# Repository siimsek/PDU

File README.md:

# Açık çevrim buck güç katı

20–26 V girişten (6S batarya, ana çalışma noktası 24,6 V) 11 V / 7,5 A (82,5 W) hedefleyen tek faz, asenkron, açık çevrim buck güç katı. Modül 0–7,5 A zarfında farklı uyumlu yükler içindir; T3 Gemstone O1 ve SLAMTEC RPLIDAR S2E referans yüklerdir.

**Aşama: ANA GÜÇ DEVRESİ.** Güç katının değerleri belirlendi ve LTspice'ta sınandı; parçalar için aday listesi var, kesin seçim yapılmadı. PWM, geri besleme ve soft-start henüz yok; fiziksel devre kurulmadı.

**Güncel yol:** Önce gereksinimler ve kontrol/sürücü/koruma mimarisi belirlenir; sonra kontrolcü ile güç katı adayları birlikte değerlendirilir ve parçalar kullanıcıyla kesinleştirilir. Bobin için 33 µH başlangıç hedefidir; kapalı çevrim uyumu ve gerçek sarım ölçümü henüz yoktur. Devamında gerçek değerlerle simülasyon ve tezgâh doğrulaması yapılır. [Yol haritası](YOL-HARITASI.md) bağımlılıkları ve açık işleri gösterir.

**Dondurma durumu: FROZEN (12 Kasım 2026, simülasyon dondurması).** Çıkışa paralel `Cd = 470 µF + seri Rd = 0,22 Ω` sönüm dalı eklendi. Örneklenen model setlerinde 200 ms ve ayrı bir köşede 500 ms sabit güç darbeleri sönümlü raporlandı; bütün yük, sıcaklık ve tolerans kombinasyonları doğrulanmış değildir. Gerilim sınıfları **Cout ve Cd ≥ 35 V**, **Cin ≥ 50 V** olarak belirlendi. Açık çevrim güvenli 11 V regülasyonu sağlamaz; fiziksel ölçüm yoktur ve hassas yükler bağlanmamalıdır. Kanıt ve kalan işler: [buck/OPTIMIZASYON.md](buck/OPTIMIZASYON.md) §12–13.

**Kontrol yöntemi araştırması:** Depodaki açık çevrim testleri ile dışarıdaki kapalı çevrim model denemeleri ayrı tutuldu. İlk LT3844, Type-III ve ortalama-akım sonuçlarının tarihçesi [OPTIMIZASYON.md](buck/OPTIMIZASYON.md) §14–15'tedir; son tekrar, ön puan ve güç katı değişikliği hesabı §16'dadır.

**Kapalı çevrim son tekrar (14 Kasım 2026):** LT3844 F sabit-frekans tepe-akım makromodeli 20 µs yük rampasında 10,794–11,165 V, 20–26–20 V / 200 ms sabit-güç koşusunda 10,904–11,043 V verdi; bobin akımından yaklaşık 99,95 kHz doğrulandı. Modeldeki 9,76 mΩ seri akım algısı direnci dondurulmuş güç yolunda yok ve 7,5 A'ta 0,549 W HESAP kaybı ekler. Type-III Ki=200 / 9 A **ideal** akım kesimi 20 µs rampasında 9,809–11,478 V verdi; yüksüz 20 V için tamamlanmış 120 ms simülasyonda 48 ms referans rampasıyla çıkış 11,413 V tepe / 11,410 V geç değer oldu. Histeretik 25 mV modelinin çıkış aralığı daha dardı, ancak frekansı girişe göre 93,7–121,2 kHz değiştirdi. 100 kHz için LT3844 tipi kontrol en güçlü dinamik referans; güç yolu aynen korunacaksa gerçek akım algısı henüz kanıtlanmadı. Aynı puanlama altında 90 üzeri ön puan kuramsal olarak mümkün, ancak güç katı uyumunu ve kaybı iyileştirmek tek başına yaklaşık 86 puanla sınırlı kalır; diğer puan başlıklarında da ek kanıt gerekir. DCR akım algısı düşük etkili araştırma adayıdır, henüz test edilmedi ve asenkron kata doğrudan uyumu gösterilmedi. Ön puan, hesap ve riskler [buck/OPTIMIZASYON.md](buck/OPTIMIZASYON.md) §16.4–16.7'dedir. Mimari/parça seçilmedi; bağımsız OVP doğrulanmadığından gerçek O1/S2E bağlanmaz.

**Nerede kaldık, sırada ne var:** [YOL-HARITASI.md](YOL-HARITASI.md) · **Çalışma kuralları (yapay zekâ araçları dahil):** [AGENTS.md](AGENTS.md)

## Devre değerleri ve parçalar

| Eleman | Şematikteki değer | 1. sıra aday (kesin değil) | Kabul aralığı |
|---|---|---|---|
| V1 | 24,6 V | 6S batarya | 20–26 V |
| Vdrv | 100 kHz, Ton = 4,59 µs | — (sonraki aşamada sürücü + PWM) | — |
| L1 | 33 µH el sarım, DCR 7,81 mΩ (HESAP, 20 °C) | Magnetics Kool Mµ 40µ `0077536A7`, 22 sarım, 100 × 0,20 mm litz (2. sıra: satın alma, Würth 74435583300) | **33 µH** (el sarım 30,7–36,1 µH öngörü; satın alma ±%20 için örnek köşeler sınandı); DCR 6,5–15 mΩ (el sarım hedefi 7,5–10 mΩ); 12 A'de L ≈ %95 (HESAP) |
| Cout | 1000 µF, ESR 35 mΩ (**maks. empedans, ESR varsayımı**) | Nichicon UHE1E102MHD6TO *(elektriksel R/C referansı; kesin parça ≥35 V seçilecek)* | 1000 µF ±%20, ESR ≤ 35 mΩ, **≥ 35 V** (S1 kısa devresinde 27,3–31,1 V) |
| Cd + Rd | 470 µF + seri 0,22 Ω (çıkış sönüm dalı) | — (dondurma sonrası seçilecek) | Cd: 470 µF ±%20, **≥ 35 V**; Rd: 0,22 Ω (Rd + Cd_ESR toplamı **0,15–0,60 Ω**), ≥ 0,25 W |
| Cin1, Cin2 | 2 × 1000 µF, ESR 15 mΩ | 2 × TDK B41859D7108M000 *(elektriksel R/C referansı; kesin parça ≥50 V seçilecek)* | toplam ripple akımı ≥ 4,5 A, **≥ 50 V**; örnek sıcak takma hesabı 48,0 V, gerçek kaynak ve pay doğrulanmadı |
| S1 | ideal anahtar, `Ron=5.6m` | STP100N6F7 (60 V, TO-220) | RDS(on) ≤ 12 mΩ, VDS ≥ 55 V |
| D1 | ideal diyot, `Vf=0.38 Ron=8m` | STPS40M60CT (60 V, 2 × 20 A, iki bacak paralel) | VF ≤ 0,58 V @ 7,5 A, VRRM ≥ 45 V |
| Rload | 1,467 Ω | ≥ 100 W direnç yükü | — |

Şematik ideal elemanlıdır; değerler aday listesinin başındaki parçaların veri sayfasından alınmıştır. Bu bir satın alma kararı değildir. Adayların sırası ve nedeni, doğrulama durumu ve kriterlerin nedenleri: [buck/PARCA-HEDEFLERI.md](buck/PARCA-HEDEFLERI.md). Seçim süreci ve test sonuçları: [buck/OPTIMIZASYON.md](buck/OPTIMIZASYON.md).

LTspice sonucu (24,6 V giriş, kararlı durum, 19–20 ms): Vo = 11,000 V, çıkış ripple'ı 55,7 mV t-t, bobin akımı 6,56–8,44 A. Fiziksel ölçüm yoktur.

Açık çevrim: Ton sabitken giriş veya yük değişirse çıkış 11 V'ta kalmaz; soft-start yoktur (sert kalkışta LTspice 61,4 A / 16,6 V gösterir). **Gerçek O1 veya S2E bağlanmaz.**

## LTspice'ta deneme

1. `buck/ltspice/buck_guc_kati.asc` dosyasını aç, **Run** (koşan adam simgesi) düğmesine bas.
2. `out` telinin üstüne tıkla → çıkış gerilimi. L1'in gövdesine tıkla → bobin akımı.
3. İlk ~10 ms kalkış salınımıdır; kararlı durum için 19–20 ms arasını büyüt (fareyle sürükle).
4. Grafikte iz adına (`V(out)`) **Ctrl + sol tık** → ortalama ve RMS değeri.
5. Değer değiştirmek için parçanın üstündeki değere sağ tıkla, yaz, yeniden Run. S1 ve D1 de aynı şekilde değişir (`Ron=…`, `Vf=…`).

Şematikteki tek yönerge `.tran 20m` satırıdır (simülasyon süresi); LTspice bunu şematikte ister.

Beklenen (24,6 V giriş, 19–20 ms): V(out) ortalama ≈ 11,00 V, ripple ≈ 56 mV t-t, I(L1) ≈ 6,6–8,4 A.

## Dosyalar

| Dosya | Ne işe yarar |
|---|---|
| [YOL-HARITASI.md](YOL-HARITASI.md) | Güncel durum, adımlar ve tamamlanma ölçütleri, karar günlüğü |
| [AGENTS.md](AGENTS.md) | Çalışma kuralları: neyin nasıl yapılacağı, araçlar, PCB aşaması kuralları |
| [buck/ltspice/buck_guc_kati.asc](buck/ltspice/buck_guc_kati.asc) | LTspice şematiği (çift tıkla aç, Run) |
| [buck/PARCA-HEDEFLERI.md](buck/PARCA-HEDEFLERI.md) | Aday parçalar (öncelik sırasıyla), kriterler (en az/en çok değerler) ve nedenleri, Türkiye'de bulunurluk, parça arama istemi |
| [buck/OPTIMIZASYON.md](buck/OPTIMIZASYON.md) | Yük gereksinimleri, değerlerin nasıl seçildiği, test sonuçları, açık riskler |
| [buck/hesap.py](buck/hesap.py) | Analitik hesap: ripple, akımlar, LC dinamiği, sabit güç yükü kararlılığı, kayıp ve ısı bütçesi, gerilim sınıfları (`python buck/hesap.py`) |
| [buck/dogrula.py](buck/dogrula.py) | LTspice doğrulama koşuları (`python buck/dogrula.py secilen` / `pencere` / `kararlilik` / `zarf` / `stres` / `sayisal` / `tarama` / `grafik`) |
| `buck/grafik/*.svg` | `dogrula.py grafik` ile üretilen dalga şekilleri |
| `buck/ltspice/anahtar.asy`, `diyot.asy`, `idealler.lib` | İdeal anahtar ve diyot parçaları; şematikle aynı klasörde durmalı, elle açmak gerekmez |
| [buck/ltspice/sematik_uret.py](buck/ltspice/sematik_uret.py), [asc_gorsel.py](buck/ltspice/asc_gorsel.py) | Şematiği ve yukarıdaki görseli üretir |
| [CLAUDE.md](CLAUDE.md) | Claude Code için `AGENTS.md` ve `YOL-HARITASI.md` dosyalarına yönlendirme |

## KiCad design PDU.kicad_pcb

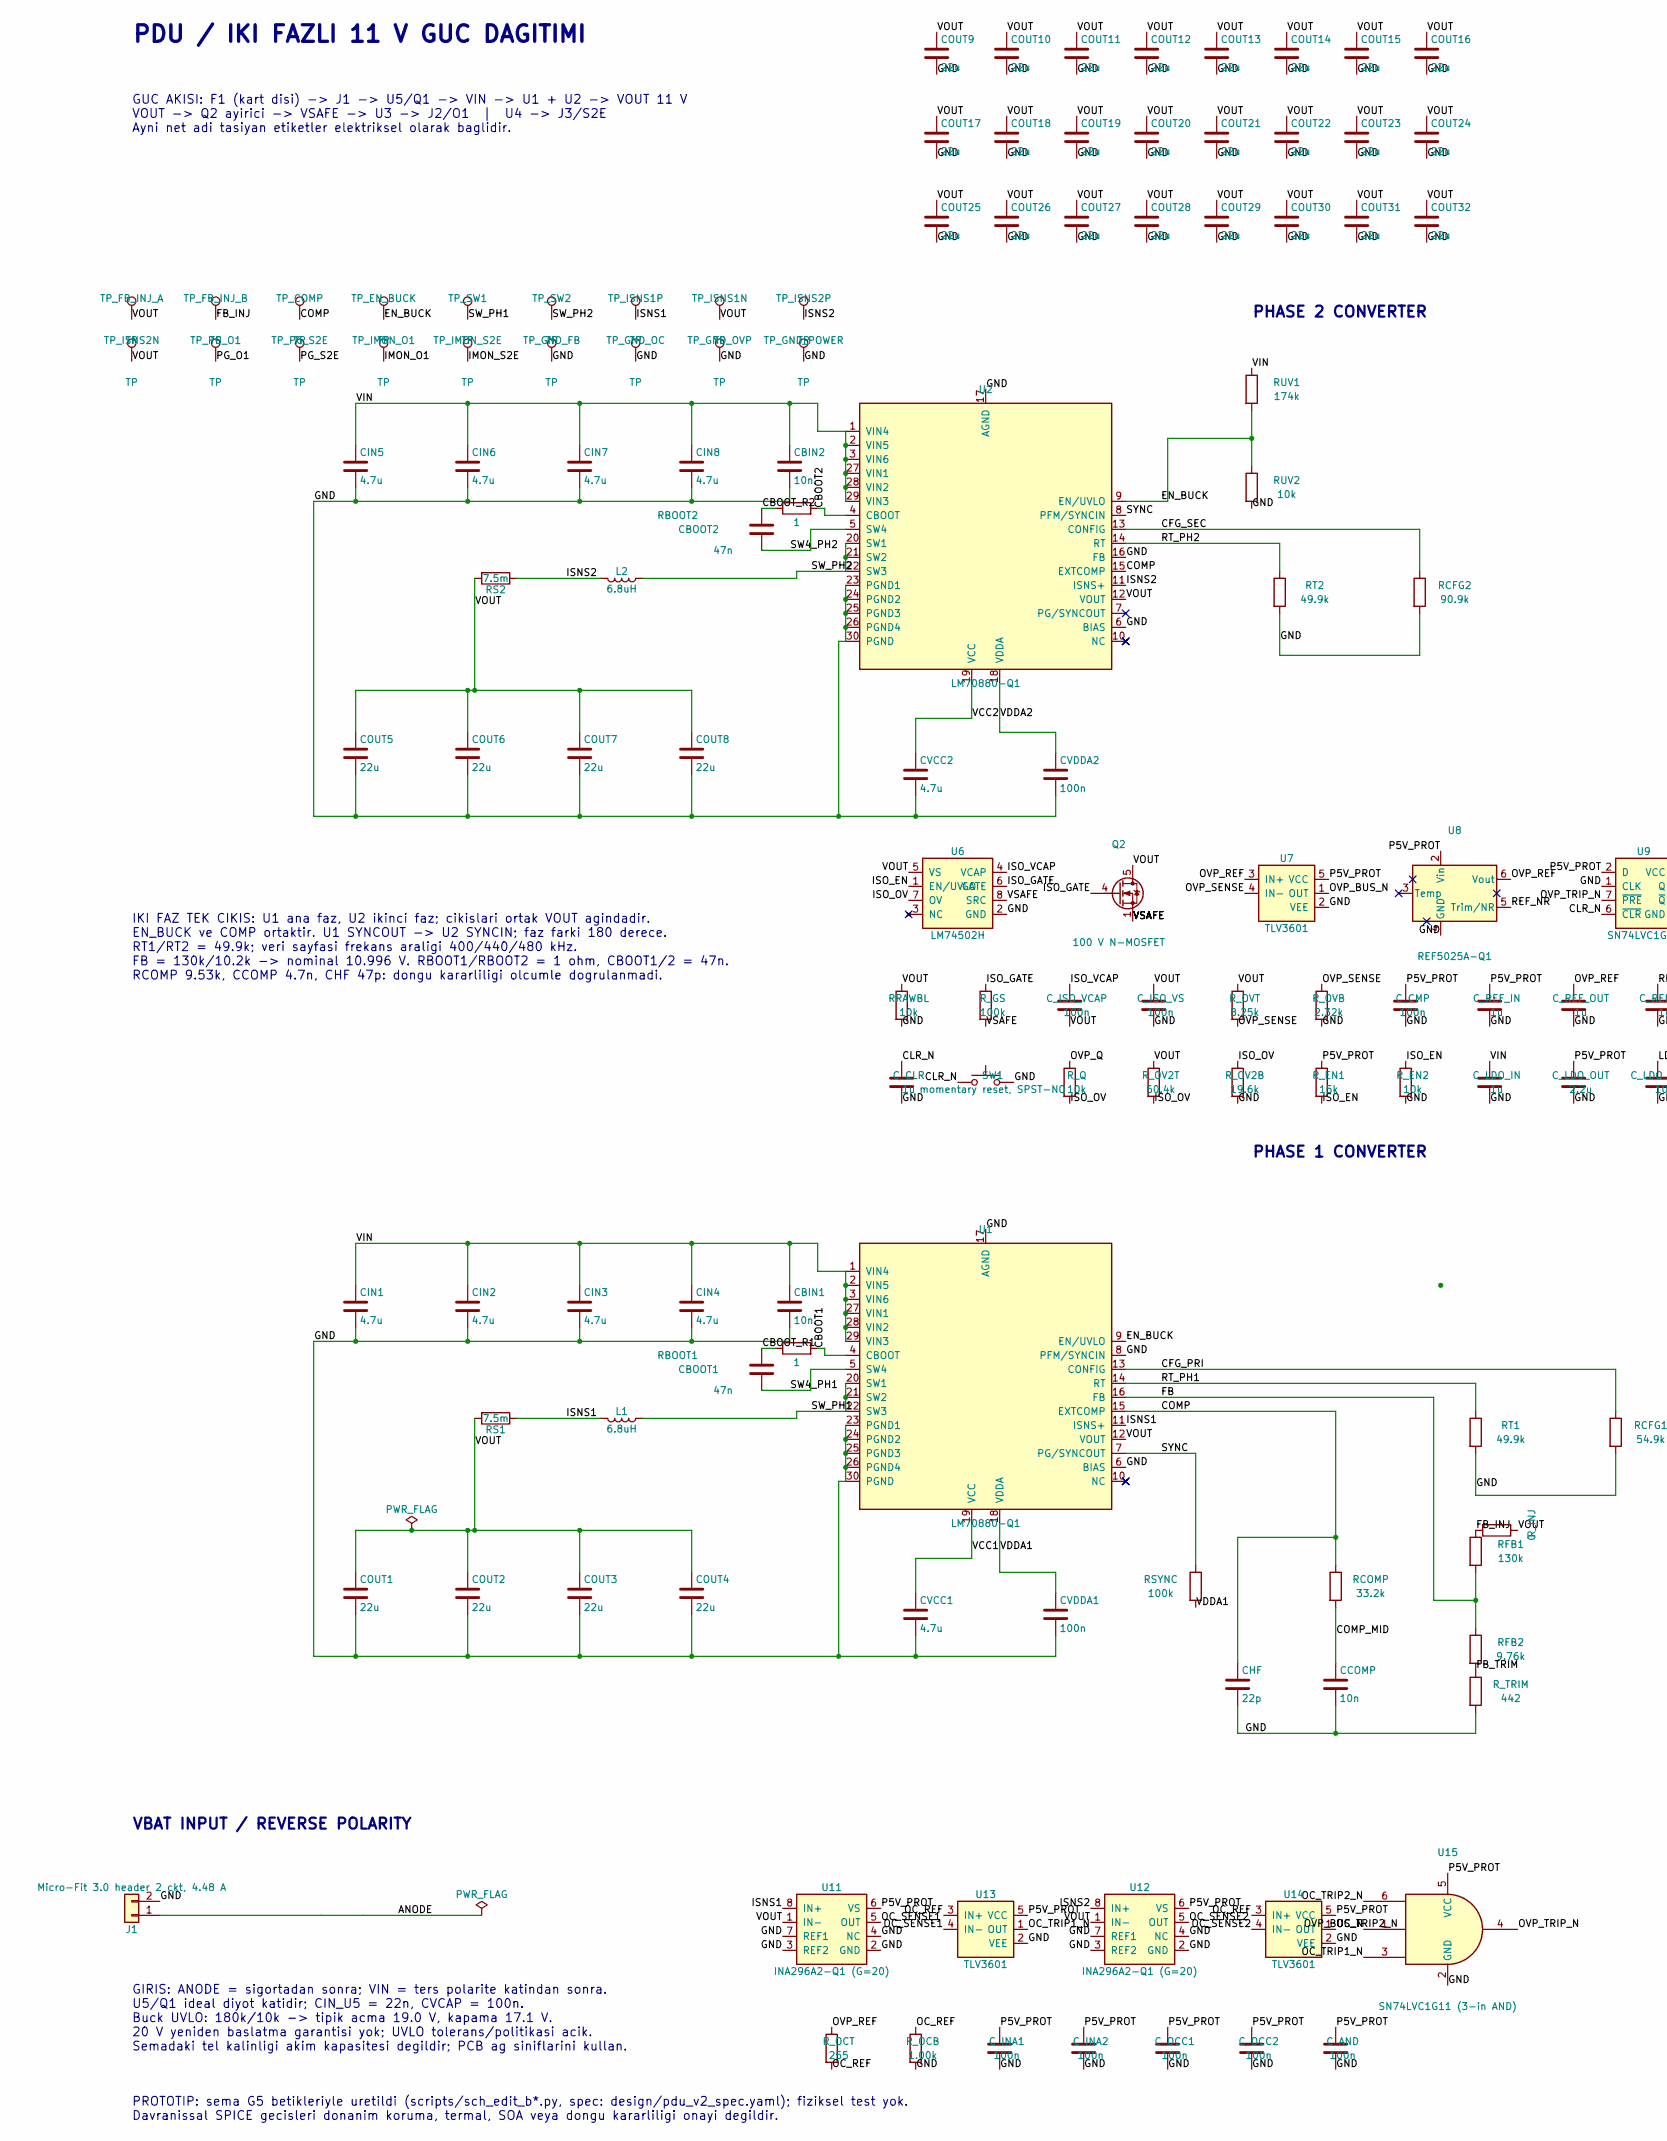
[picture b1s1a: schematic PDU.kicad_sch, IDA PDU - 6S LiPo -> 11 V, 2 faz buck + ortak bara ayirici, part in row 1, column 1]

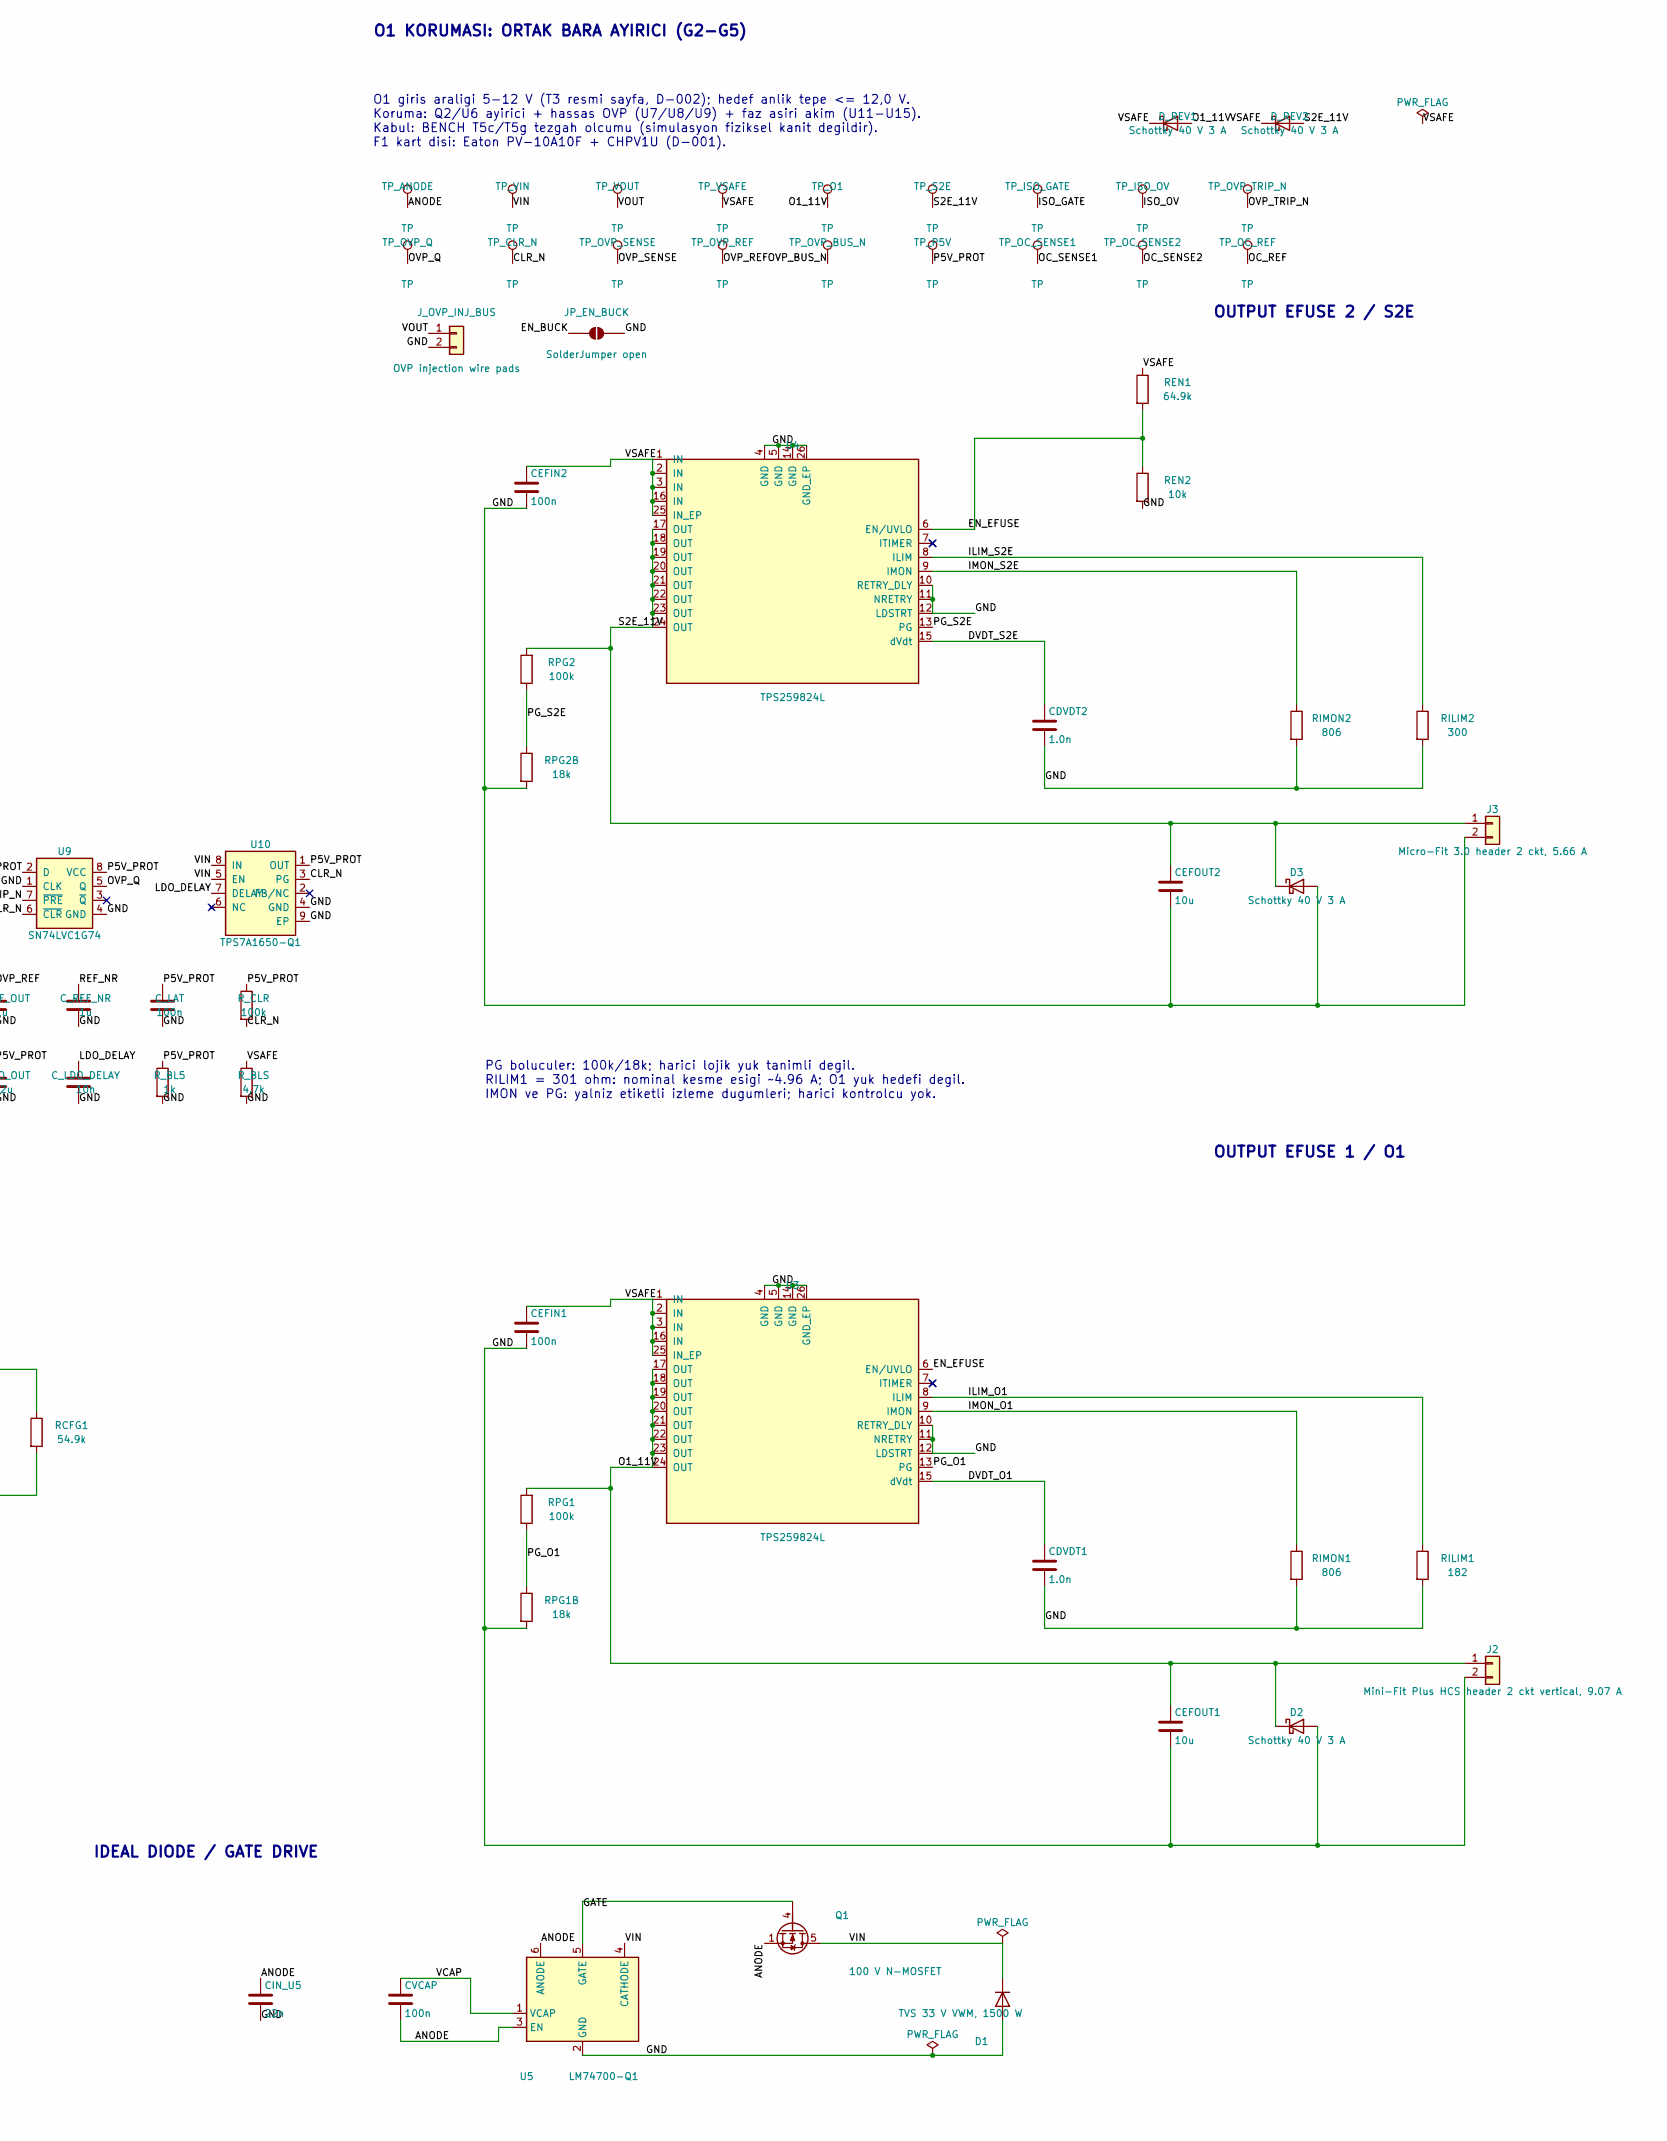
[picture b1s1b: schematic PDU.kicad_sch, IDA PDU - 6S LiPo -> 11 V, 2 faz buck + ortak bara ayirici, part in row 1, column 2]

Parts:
CBIN1, CBIN2: 10n; C_0603_1608Metric; MPN C1608X7R2A103K080AA
CBOOT1, CBOOT2: 47n; C_0603_1608Metric; MPN C1608X7R1H473K080AA
CCOMP: 10n; C_0603_1608Metric; MPN C1608C0G1H103J080AA
CDVDT1, CDVDT2: 1.0n; C_0603_1608Metric; MPN C1608C0G1H102J080AA
CEFIN1, CEFIN2: 100n; C_0603_1608Metric; MPN C1608X7R1H104K080AA
CEFOUT1, CEFOUT2: 10u; C_1206_3216Metric; MPN C3216X7R1E106K160AB
CHF: 22p; C_0603_1608Metric; MPN C1608C0G1H220J080AA
CIN1, CIN2, CIN3, CIN4, CIN5, CIN6, CIN7, CIN8: 4.7u; C_1210_3225Metric; MPN C3225X7S2A475K200AB
CIN_U5: 22n; C_0603_1608Metric; MPN C1608X7R2A223K080AA
COUT1, COUT2, COUT3, COUT4, COUT5, COUT6, COUT7, COUT8: 22u; TDK_C5750_2220_Recommended; Tolerance 20%; Voltage 100V; MPN C5750X7S2A226M280KB
COUT9, COUT10, COUT11, COUT12, COUT13, COUT14, COUT15, COUT16, COUT17, COUT18, COUT19, COUT20, COUT21, COUT22, COUT23, COUT24, COUT25, COUT26, COUT27, COUT28, COUT29, COUT30, COUT31, COUT32: 22u; TDK_C5750_2220_Recommended; Voltage 100V; MPN C5750X7S2A226M280KB
CVCAP: 100n; C_0603_1608Metric; MPN C1608X7R1H104K080AA
CVCC1, CVCC2: 4.7u; C_0805_2012Metric; MPN C2012X7R1E475K125AB
CVDDA1, CVDDA2: 100n; C_0603_1608Metric; MPN C1608X7R1H104K080AA
C_AND: 100n; C_0603_1608Metric; MPN C1608X7R1H104K080AA
C_CLR: 1u; C_0603_1608Metric; MPN C1608X7R1E105K080AB
C_CMP: 100n; C_0603_1608Metric; MPN C1608X7R1H104K080AA
C_INA1, C_INA2: 100n; C_0603_1608Metric; MPN C1608X7R1H104K080AA
C_ISO_VCAP: 100n; C_0603_1608Metric; MPN C1608X7R1H104K080AA
C_ISO_VS: 100n; C_0603_1608Metric; MPN C1608X7S2A104K080AB
C_LAT: 100n; C_0603_1608Metric; MPN C1608X7R1H104K080AA
C_LDO_DELAY: 10n; C_0603_1608Metric; MPN C1608C0G1H103J080AA
C_LDO_IN: 1u; C_1206_3216Metric; MPN C3216X7R2A105K160AA
C_LDO_OUT: 2.2u; C_0805_2012Metric; MPN C2012X7R1E225K125AB
C_OCC1, C_OCC2: 100n; C_0603_1608Metric; MPN C1608X7R1H104K080AA
C_REF_IN: 1u; C_0603_1608Metric; MPN C1608X7R1E105K080AB
C_REF_NR: 1u; C_0603_1608Metric; MPN C1608X7R1E105K080AB
C_REF_OUT: 1u; C_0603_1608Metric; MPN C1608X7R1E105K080AB
D1: TVS 33 V VWM, 1500 W; D_SMC; MPN SMCJ33A-E3/57T
D2, D3: Schottky 40 V 3 A; D_SMC; MPN SS34-E3/57T
D_REV1, D_REV2: Schottky 40 V 3 A; D_SMC; MPN SS34-E3/57T
J1: Micro-Fit 3.0 header 2 ckt, 4.48 A; Molex_Micro-Fit_3.0_43045-0200_2x01_P3.00mm_Horizontal; MPN 430450200
J2: Mini-Fit Plus HCS header 2 ckt vertical, 9.07 A; Molex_Mini-Fit_Jr_5566-02A_2x01_P4.20mm_Vertical; MPN 460150206
J3: Micro-Fit 3.0 header 2 ckt, 5.66 A; Molex_Micro-Fit_3.0_43045-0200_2x01_P3.00mm_Horizontal; MPN 430450200
JP_EN_BUCK: SolderJumper open; SolderJumper-2_P1.3mm_Open_RoundedPad1.0x1.5mm
J_OVP_INJ_BUS: OVP injection wire pads; SolderWire-6sqmm_1x02_P14mm_D3.5mm_OD7mm
L1, L2: 6.8uH; L_Vishay_IHLP-4040; MPN IHLP4040DZER6R8M01
Q1: 100 V N-MOSFET; TDSON-8-1_Konnect; MPN BSC160N10NS3G
Q2: 100 V N-MOSFET; TI_CSD19531Q5A_Q5A; MPN CSD19531Q5A
RBOOT1, RBOOT2: 1; R_0603_1608Metric; MPN CRCW06031R00FKEA
RCFG1: 54.9k; R_0603_1608Metric; MPN CRCW060354K9FKEA
RCFG2: 90.9k; R_0603_1608Metric; MPN CRCW060390K9FKEA
RCOMP: 33.2k; R_0603_1608Metric; MPN CRCW060333K2FKEA
REN1: 64.9k; R_0603_1608Metric; MPN CRCW060364K9FKEA
REN2: 10k; R_0603_1608Metric; MPN CRCW060310K0FKEA
RFB1: 130k; R_0603_1608Metric; Tolerance 0.1%; MPN ERA3AEB134V
RFB2: 9.76k; R_0603_1608Metric; MPN TNPW06039K76BXEA
RILIM1: 182; R_0603_1608Metric; MPN TNPW0603182RBXEA
RILIM2: 300; R_0603_1608Metric; MPN TNPW0603300RBXEA
RIMON1, RIMON2: 806; R_0603_1608Metric; Tolerance 0.1%; MPN ERA3AEB8060V
RPG1, RPG2: 100k; R_0603_1608Metric; MPN CRCW0603100KFKEA
RPG1B, RPG2B: 18k; R_0603_1608Metric; MPN CRCW060318K0FKEA
RRAWBL: 10k; R_1206_3216Metric; MPN CRCW120610K0FKEA
RS1, RS2: 7.5m; R_2512_6332Metric; MPN WSL25127L500FEA
RSYNC: 100k; R_0603_1608Metric; MPN CRCW0603100KFKEA
RT1, RT2: 49.9k; R_0603_1608Metric; MPN CRCW060349K9FKEA
RUV1: 174k; R_0603_1608Metric; MPN TNPW0603174KBEEA
RUV2: 10k; R_0603_1608Metric; MPN TNPW060310K0BEEA
R_BL5: 1k; R_1206_3216Metric; MPN CRCW12061K00FKEA
R_BLS: 4.7k; R_1206_3216Metric; MPN CRCW12064K70FKEA
R_CLR: 100k; R_0603_1608Metric; MPN CRCW0603100KFKEA
R_EN1: 15k; R_0603_1608Metric; MPN CRCW060315K0FKEA
R_EN2: 10k; R_0603_1608Metric; MPN CRCW060310K0FKEA
R_GS: 100k; R_0603_1608Metric; MPN CRCW0603100KFKEA
R_INJ: 0; R_0603_1608Metric; MPN CRCW06030000Z0EA
R_OCB: 1.00k; R_0603_1608Metric; MPN TNPW06031K00BXEA
R_OCT: 255; R_0603_1608Metric; MPN TNPW0603255RBXEA
R_OV2B: 19.6k; R_0603_1608Metric; MPN CRCW060319K6FKEA
R_OV2T: 60.4k; R_0603_1608Metric; MPN CRCW060360K4FKEA
R_OVB: 2.32k; R_1206_3216Metric; MPN TNPW12062K32BXEA
R_OVT: 8.25k; R_1206_3216Metric; MPN TNPW12068K25BXEA
R_Q: 10k; R_0603_1608Metric; MPN CRCW060310K0FKEA
R_TRIM: 442; R_0603_1608Metric; MPN TNPW0603442RBXEA
SW1: momentary reset, SPST-NO; SW_SPST_B3U-1000P; MPN B3U-1000P
TP_ANODE: TP; TestPoint_Pad_D2.0mm
TP_CLR_N: TP; TestPoint_Pad_D1.0mm
TP_COMP: TP; TestPoint_Pad_D1.0mm
TP_EN_BUCK: TP; TestPoint_Pad_D1.0mm
TP_FB_INJ_A: TP; TestPoint_Pad_D1.0mm
TP_FB_INJ_B: TP; TestPoint_Pad_D1.0mm
TP_GND_FB: TP; TestPoint_Pad_D2.0mm
TP_GND_OC: TP; TestPoint_Pad_D2.0mm
TP_GND_OVP: TP; TestPoint_Pad_D2.0mm
TP_GND_POWER: TP; TestPoint_Pad_D2.0mm
TP_IMON_O1: TP; TestPoint_Pad_D1.0mm
TP_IMON_S2E: TP; TestPoint_Pad_D1.0mm
TP_ISNS1N, TP_ISNS1P, TP_ISNS2N, TP_ISNS2P: TP; TestPoint_Pad_D1.0mm
TP_ISO_GATE: TP; TestPoint_Pad_D1.0mm
TP_ISO_OV: TP; TestPoint_Pad_D1.0mm
TP_O1: TP; TestPoint_Pad_D2.0mm
TP_OC_REF: TP; TestPoint_Pad_D1.0mm
TP_OC_SENSE1, TP_OC_SENSE2: TP; TestPoint_Pad_D1.0mm
TP_OVP_BUS_N: TP; TestPoint_Pad_D1.0mm
TP_OVP_Q: TP; TestPoint_Pad_D1.0mm
TP_OVP_REF: TP; TestPoint_Pad_D1.0mm
TP_OVP_SENSE: TP; TestPoint_Pad_D1.0mm
TP_OVP_TRIP_N: TP; TestPoint_Pad_D1.0mm
TP_P5V: TP; TestPoint_Pad_D1.0mm
TP_PG_O1: TP; TestPoint_Pad_D1.0mm
TP_PG_S2E: TP; TestPoint_Pad_D1.0mm
TP_S2E: TP; TestPoint_Pad_D2.0mm
TP_SW1, TP_SW2: TP; TestPoint_Pad_D1.0mm
TP_VIN: TP; TestPoint_Pad_D2.0mm
TP_VOUT: TP; TestPoint_Pad_D2.0mm
TP_VSAFE: TP; TestPoint_Pad_D2.0mm
U1, U2: LM70880-Q1; LM70880_RRX0029B_RectLands; MPN LM70880QRRXRQ1
U3, U4: TPS259824L; TPS25982_RGE0024M; MPN TPS259824LNRGER
U5: LM74700-Q1; SOT-23-6; MPN LM74700QDBVRQ1
U6: LM74502H; TSOT-23-8; MPN LM74502HDDFR
U7, U13, U14: TLV3601; SOT-353_SC-70-5; MPN TLV3601DCKR
U8: REF5025A-Q1; SOIC-8_3.9x4.9mm_P1.27mm; MPN REF5025AQDRQ1
U9: SN74LVC1G74; VSSOP-8_2.3x2mm_P0.5mm; MPN SN74LVC1G74DCUR
U10: TPS7A1650-Q1; HVSSOP-8-1EP_3x3mm_P0.65mm_EP1.57x1.89mm; MPN TPS7A1650QDGNRQ1
U11, U12: INA296A2-Q1 (G=20); VSSOP-8_3x3mm_P0.65mm; MPN INA296A2QDGKRQ1
U15: SN74LVC1G11 (3-in AND); SOT-23-6; MPN SN74LVC1G11DBVR

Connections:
/ANODE: CIN_U5.1, CVCAP.2, J1.1, Q1.1 (S), Q1.2 (S), Q1.3 (S), TP_ANODE.1, U5.3 (EN), U5.6 (ANODE)
/CBOOT1: RBOOT1.2, U1.4 (CBOOT)
/CBOOT2: RBOOT2.2, U2.4 (CBOOT)
/CBOOT_R1: CBOOT1.1, RBOOT1.1
/CBOOT_R2: CBOOT2.1, RBOOT2.1
/CFG_PRI: RCFG1.1, U1.13 (CONFIG)
/CFG_SEC: RCFG2.1, U2.13 (CONFIG)
/CLR_N: C_CLR.1, R_CLR.2, SW1.1, TP_CLR_N.1, U9.6 (~CLR), U10.3 (PG)
/COMP: CHF.1, RCOMP.1, TP_COMP.1, U1.15 (EXTCOMP), U2.15 (EXTCOMP)
/COMP_MID: CCOMP.1, RCOMP.2
/DVDT_O1: CDVDT1.1, U3.15 (dVdt)
/DVDT_S2E: CDVDT2.1, U4.15 (dVdt)
/EN_BUCK: JP_EN_BUCK.1 (A), RUV1.2, RUV2.1, TP_EN_BUCK.1, U1.9 (EN/UVLO), U2.9 (EN/UVLO)
/EN_EFUSE: REN1.2, REN2.1, U3.6 (EN/UVLO), U4.6 (EN/UVLO)
/FB: RFB1.2, RFB2.1, U1.16 (FB)
/FB_INJ: RFB1.1, R_INJ.2, TP_FB_INJ_B.1
/FB_TRIM: RFB2.2, R_TRIM.1
/GATE: Q1.4 (G), U5.5 (GATE)
/GND: CBIN1.2, CBIN2.2, CCOMP.2, CDVDT1.2, CDVDT2.2, CEFIN1.2, CEFIN2.2, CEFOUT1.2, CEFOUT2.2, CHF.2, CIN1.2, CIN2.2, CIN3.2, CIN4.2, CIN5.2, CIN6.2, CIN7.2, CIN8.2, CIN_U5.2, COUT1.2, COUT2.2, COUT3.2, COUT4.2, COUT5.2, COUT6.2, COUT7.2, COUT8.2, COUT9.2, COUT10.2, COUT11.2, COUT12.2, COUT13.2, COUT14.2, COUT15.2, COUT16.2, COUT17.2, COUT18.2, COUT19.2, COUT20.2, COUT21.2, COUT22.2, COUT23.2, COUT24.2, COUT25.2, COUT26.2, COUT27.2, COUT28.2, COUT29.2, COUT30.2, COUT31.2, COUT32.2, CVCC1.2, CVCC2.2, CVDDA1.2, CVDDA2.2, C_AND.2, C_CLR.2, C_CMP.2, C_INA1.2, C_INA2.2, C_ISO_VS.2, C_LAT.2, C_LDO_DELAY.2, C_LDO_IN.2, C_LDO_OUT.2, C_OCC1.2, C_OCC2.2, C_REF_IN.2, C_REF_NR.2, C_REF_OUT.2, D1.2 (A), D2.2 (A), D3.2 (A), J1.2, J2.2, J3.2, JP_EN_BUCK.2 (B), J_OVP_INJ_BUS.2, RCFG1.2, RCFG2.2, REN2.2, RILIM1.2, RILIM2.2, RIMON1.2, RIMON2.2, RPG1B.2, RPG2B.2, RRAWBL.2, RT1.2, RT2.2, RUV2.2, R_BL5.2, R_BLS.2, R_EN2.2, R_OCB.2, R_OV2B.2, R_OVB.2, R_TRIM.2, SW1.2, TP_GND_FB.1, TP_GND_OC.1, TP_GND_OVP.1, TP_GND_POWER.1, U1.6 (BIAS), U1.8 (PFM/SYNCIN), U1.17 (AGND), U1.23 (PGND1), U1.24 (PGND2), U1.25 (PGND3), U1.26 (PGND4), U1.30 (PGND), U2.6 (BIAS), U2.16 (FB), U2.17 (AGND), U2.23 (PGND1), U2.24 (PGND2), U2.25 (PGND3), U2.26 (PGND4), U2.30 (PGND), U3.4 (GND), U3.5 (GND), U3.10 (RETRY_DLY), U3.11 (NRETRY), U3.12 (LDSTRT), U3.14 (GND), U3.26 (GND_EP), U4.4 (GND), U4.5 (GND), U4.10 (RETRY_DLY), U4.11 (NRETRY), U4.12 (LDSTRT), U4.14 (GND), U4.26 (GND_EP), U5.2 (GND), U6.2 (GND), U7.2 (VEE), U8.4 (GND), U9.1 (CLK), U9.4 (GND), U10.4 (GND), U10.9 (EP), U11.2 (GND), U11.3 (REF2), U11.4 (NC), U11.7 (REF1), U12.2 (GND), U12.3 (REF2), U12.4 (NC), U12.7 (REF1), U13.2 (VEE), U14.2 (VEE), U15.2 (GND)
/ILIM_O1: RILIM1.1, U3.8 (ILIM)
/ILIM_S2E: RILIM2.1, U4.8 (ILIM)
/IMON_O1: RIMON1.1, TP_IMON_O1.1, U3.9 (IMON)
/IMON_S2E: RIMON2.1, TP_IMON_S2E.1, U4.9 (IMON)
/ISNS1: L1.2, RS1.1, TP_ISNS1P.1, U1.11 (ISNS+), U11.8 (IN+)
/ISNS2: L2.2, RS2.1, TP_ISNS2P.1, U2.11 (ISNS+), U12.8 (IN+)
/ISO_EN: R_EN1.2, R_EN2.1, U6.1 (EN/UVLO)
/ISO_GATE: Q2.4 (G), R_GS.1, TP_ISO_GATE.1, U6.6 (GATE)
/ISO_OV: R_OV2B.1, R_OV2T.2, R_Q.2, TP_ISO_OV.1, U6.7 (OV)
/ISO_VCAP: C_ISO_VCAP.1, U6.4 (VCAP)
/LDO_DELAY: C_LDO_DELAY.1, U10.7 (DELAY)
/O1_11V: CEFOUT1.1, D2.1 (K), D_REV1.2 (A), J2.1, RPG1.2, TP_O1.1, U3.17 (OUT), U3.18 (OUT), U3.19 (OUT), U3.20 (OUT), U3.21 (OUT), U3.22 (OUT), U3.23 (OUT), U3.24 (OUT)
/OC_REF: R_OCB.1, R_OCT.2, TP_OC_REF.1, U13.3 (IN+), U14.3 (IN+)
/OC_SENSE1: TP_OC_SENSE1.1, U11.5 (OUT), U13.4 (IN-)
/OC_SENSE2: TP_OC_SENSE2.1, U12.5 (OUT), U14.4 (IN-)
/OC_TRIP1_N: U13.1 (OUT), U15.3
/OC_TRIP2_N: U14.1 (OUT), U15.6
/OVP_BUS_N: TP_OVP_BUS_N.1, U7.1 (OUT), U15.1
/OVP_Q: R_Q.1, TP_OVP_Q.1, U9.5 (Q)
/OVP_REF: C_REF_OUT.1, R_OCT.1, TP_OVP_REF.1, U7.3 (IN+), U8.6 (Vout)
/OVP_SENSE: R_OVB.1, R_OVT.2, TP_OVP_SENSE.1, U7.4 (IN-)
/OVP_TRIP_N: TP_OVP_TRIP_N.1, U9.7 (~PRE), U15.4
/P5V_PROT: C_AND.1, C_CMP.1, C_INA1.1, C_INA2.1, C_LAT.1, C_LDO_OUT.1, C_OCC1.1, C_OCC2.1, C_REF_IN.1, R_BL5.1, R_CLR.1, R_EN1.1, TP_P5V.1, U7.5 (VCC), U8.2 (Vin), U9.2 (D), U9.8 (VCC), U10.1 (OUT), U11.6 (VS), U12.6 (VS), U13.5 (VCC), U14.5 (VCC), U15.5 (VCC)
/PG_O1: RPG1.1, RPG1B.1, TP_PG_O1.1, U3.13 (PG)
/PG_S2E: RPG2.1, RPG2B.1, TP_PG_S2E.1, U4.13 (PG)
/REF_NR: C_REF_NR.1, U8.5 (Trim/NR)
/RT_PH1: RT1.1, U1.14 (RT)
/RT_PH2: RT2.1, U2.14 (RT)
/S2E_11V: CEFOUT2.1, D3.1 (K), D_REV2.2 (A), J3.1, RPG2.2, TP_S2E.1, U4.17 (OUT), U4.18 (OUT), U4.19 (OUT), U4.20 (OUT), U4.21 (OUT), U4.22 (OUT), U4.23 (OUT), U4.24 (OUT)
/SW4_PH1: CBOOT1.2, U1.5 (SW4)
/SW4_PH2: CBOOT2.2, U2.5 (SW4)
/SW_PH1: L1.1, TP_SW1.1, U1.20 (SW1), U1.21 (SW2), U1.22 (SW3)
/SW_PH2: L2.1, TP_SW2.1, U2.20 (SW1), U2.21 (SW2), U2.22 (SW3)
/SYNC: RSYNC.1, U1.7 (PG/SYNCOUT), U2.8 (PFM/SYNCIN)
/VCAP: CVCAP.1, U5.1 (VCAP)
/VCC1: CVCC1.1, U1.19 (VCC)
/VCC2: CVCC2.1, U2.19 (VCC)
/VDDA1: CVDDA1.1, RSYNC.2, U1.18 (VDDA)
/VDDA2: CVDDA2.1, U2.18 (VDDA)
/VIN: CBIN1.1, CBIN2.1, CIN1.1, CIN2.1, CIN3.1, CIN4.1, CIN5.1, CIN6.1, CIN7.1, CIN8.1, C_LDO_IN.1, D1.1 (K), Q1.5 (D), RUV1.1, TP_VIN.1, U1.1 (VIN4), U1.2 (VIN5), U1.3 (VIN6), U1.27 (VIN1), U1.28 (VIN2), U1.29 (VIN3), U2.1 (VIN4), U2.2 (VIN5), U2.3 (VIN6), U2.27 (VIN1), U2.28 (VIN2), U2.29 (VIN3), U5.4 (CATHODE), U10.5 (EN), U10.8 (IN)
/VOUT: COUT1.1, COUT2.1, COUT3.1, COUT4.1, COUT5.1, COUT6.1, COUT7.1, COUT8.1, COUT9.1, COUT10.1, COUT11.1, COUT12.1, COUT13.1, COUT14.1, COUT15.1, COUT16.1, COUT17.1, COUT18.1, COUT19.1, COUT20.1, COUT21.1, COUT22.1, COUT23.1, COUT24.1, COUT25.1, COUT26.1, COUT27.1, COUT28.1, COUT29.1, COUT30.1, COUT31.1, COUT32.1, C_ISO_VCAP.2, C_ISO_VS.1, J_OVP_INJ_BUS.1, Q2.5 (D), RRAWBL.1, RS1.2, RS2.2, R_INJ.1, R_OV2T.1, R_OVT.1, TP_FB_INJ_A.1, TP_ISNS1N.1, TP_ISNS2N.1, TP_VOUT.1, U1.12 (VOUT), U2.12 (VOUT), U6.5 (VS), U11.1 (IN-), U12.1 (IN-)
/VSAFE: CEFIN1.1, CEFIN2.1, D_REV1.1 (K), D_REV2.1 (K), Q2.1 (S), Q2.2 (S), Q2.3 (S), REN1.1, R_BLS.1, R_GS.2, TP_VSAFE.1, U3.1 (IN), U3.2 (IN), U3.3 (IN), U3.16 (IN), U3.25 (IN_EP), U4.1 (IN), U4.2 (IN), U4.3 (IN), U4.16 (IN), U4.25 (IN_EP), U6.8 (SRC)

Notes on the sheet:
VBAT INPUT / REVERSE POLARITY
IDEAL DIODE / GATE DRIVE
PHASE 2 CONVERTER
PHASE 1 CONVERTER
OUTPUT EFUSE 2 / S2E
OUTPUT EFUSE 1 / O1
PDU / IKI FAZLI 11 V GUC DAGITIMI
GUC AKISI: F1 (kart disi) -> J1 -> U5/Q1 -> VIN -> U1 + U2 -> VOUT 11 V VOUT -> Q2 ayirici -> VSAFE -> U3 -> J2/O1 | U4 -> J3/S2E Ayni net adi tasiyan etiketler elektriksel olarak baglidir.
O1 KORUMASI: ORTAK BARA AYIRICI (G2-G5)
O1 giris araligi 5-12 V (T3 resmi sayfa, D-002); hedef anlik tepe <= 12,0 V. Koruma: Q2/U6 ayirici + hassas OVP (U7/U8/U9) + faz asiri akim (U11-U15). Kabul: BENCH T5c/T5g tezgah olcumu (simulasyon fiziksel kanit degildir). F1 kart disi: Eaton PV-10A10F + CHPV1U (D-001).
IKI FAZ TEK CIKIS: U1 ana faz, U2 ikinci faz; cikislari ortak VOUT agindadir. EN_BUCK ve COMP ortaktir. U1 SYNCOUT -> U2 SYNCIN; faz farki 180 derece. RT1/RT2 = 49.9k; veri sayfasi frekans araligi 400/440/480 kHz. FB = 130k/10.2k -> nominal 10.996 V. RBOOT1/RBOOT2 = 1 ohm, CBOOT1/2 = 47n. RCOMP 9.5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
PG boluculer: 100k/18k; harici lojik yuk tanimli degil. RILIM1 = 301 ohm: nominal kesme esigi ~4.96 A; O1 yuk hedefi degil. IMON ve PG: yalniz etiketli izleme dugumleri; harici kontrolcu yok.
PROTOTIP: sema G5 betikleriyle uretildi (scripts/sch_edit_b*.py, spec: design/pdu_v2_spec.yaml); fiziksel test yok. Davranissal SPICE gecisleri donanim koruma, termal, SOA veya dongu kararliligi onayi degildir.
GIRIS: ANODE = sigortadan sonra; VIN = ters polarite katindan sonra. U5/Q1 ideal diyot katidir; CIN_U5 = 22n, CVCAP = 100n. Buck UVLO: 180k/10k -> tipik acma 19.0 V, kapama 17.1 V. 20 V yeniden baslatma garantisi yok; UVLO tolerans/politikasi acik. Semadaki tel kalinligi akim kapasitesi degildir; P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

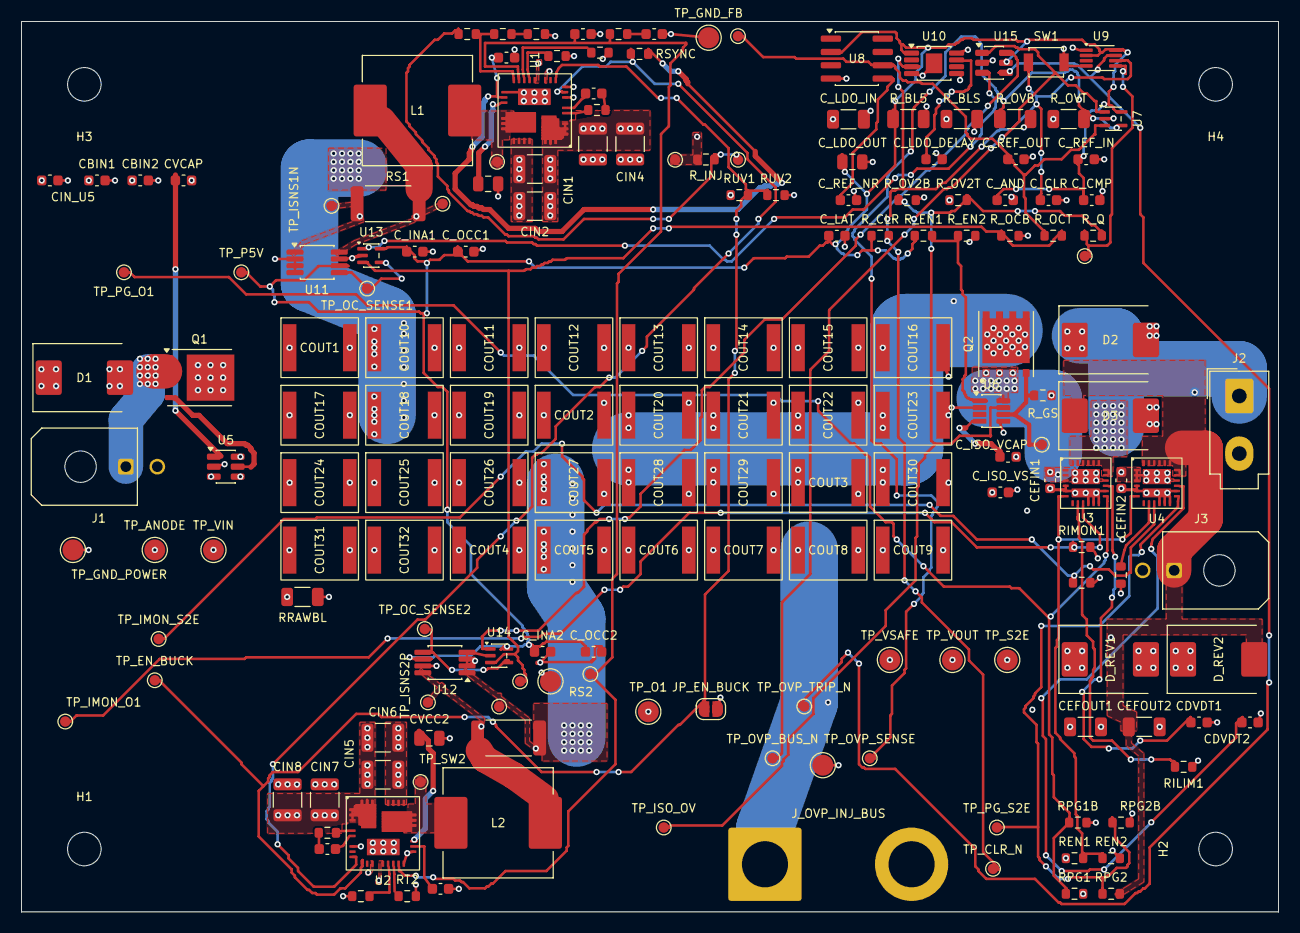
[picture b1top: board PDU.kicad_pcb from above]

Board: 4 copper layers, 120.0 x 85.0 mm, 184 parts (0 on the bottom side), 61 nets.

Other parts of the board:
H1, H2, H3, H4: MountingHole_3.2mm_M3
